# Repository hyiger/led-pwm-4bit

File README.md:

# led-pwm-4bit

A 40 × 30 mm two-layer board that dims a 24 V LED strip to one of 16 levels set by
four open-drain outputs of a Prusa GPIO Hackerboard. An ATtiny412 reads the 4-bit
word and drives a low-side N-MOSFET with 10-bit PWM at about 2.4 kHz.

KiCad 10 project. The design brief is [docs/spec.md](docs/spec.md) and the
reference netlist is [docs/netlist.txt](docs/netlist.txt).

## Status

| Step | State |
|---|---|
| Schematic | Done. ERC: 0 violations. `check_netlist.py`: matches `docs/netlist.txt` |
| Placement | Done. Schematic parity clean |
| Routing | In progress. DRC: 0 violations; 5 unrouted connections (three `HB_GND` links to F2, UPDI_BUS R11–D3, SEL3 C8–R10). GND pours stitched with 32 vias |
| Parts | Every line has a manufacturer part carried by Mouser; see [Parts](#parts) |
| Firmware | Not started (spec section 9) |

## Files

| Path | Contents |
|---|---|
| `led-pwm-4bit.kicad_pro` | Project: JLCPCB constraints, net classes (Default, Power) |
| `led-pwm-4bit.kicad_sch` | Schematic, one sheet, KiCad standard symbols only |
| `led-pwm-4bit.kicad_pcb` | Board |
| `led-pwm-4bit.kicad_dru` | Custom DRC rules (JLCPCB limits, 0.5 mm power tracks) |
| `check_netlist.py` | Compares the schematic netlist with `docs/netlist.txt` |
| `scripts/export-fab.sh` | Runs ERC, netlist check and DRC, then writes `fab/` |
| `fab/` | Schematic PDF, BOM, Mouser order CSV, position file, renders; Gerbers once DRC is clean |

## Parts

All parts are chosen from manufacturers Mouser stocks, and each was checked against
its manufacturer's datasheet for package, pinout and ratings. Capacitor values were
also checked against DC-bias data.
`fab/led-pwm-4bit-bom.csv` is the full BOM and `fab/led-pwm-4bit-mouser-order.csv`
is in Mouser's BOM-tool format (`BOARDS=n scripts/export-fab.sh` scales it). The
order rounds the resistors, capacitors and D3 up to at least 10 with spares, which
costs less than the exact count at Mouser's single-piece prices.

The Mouser part-number column is left empty on purpose. Mouser blocks automated
access, so no Mouser number could be read off its live listing, and a guessed
number can import cleanly and still be the wrong part. Mouser's BOM tool matches
each line on the manufacturer part number instead. Once a Mouser number is
confirmed, add a field named `Mouser` to that symbol and the export carries it.

| Ref | Part | Notes |
|---|---|---|
| U1 | Microchip MCP1792T-3302H/CB | 55 V input LDO, SOT-23A |
| U2 | Microchip ATTINY412-SSN | Tube; ATtiny212-SSN also fits |
| Q1 | ROHM RTR030N05HZGTL | 45 V, RDS(on) ≤ 95 mΩ at VGS 2.5 V. The 60 V IRLML0060 is not rated below 4.5 V gate drive |
| D1, D2 | Diodes Inc B160-13-F | 60 V 1 A Schottky, SMA |
| D3 | onsemi BAT54HT1G | SOD-323, pin 1 cathode (BAT54J is out of stock at Mouser) |
| F1 | Littelfuse 1812L050/60MR | 0.5 A hold, 60 V, Imax 10 A |
| F2 | Bel Fuse 0ZCG0010FF2C | 0.1 A hold, 60 V, Imax 100 A; Hackerboard/programmer ground return |
| C1 | Murata GRM188R61H225KE11D | 2.2 µF 50 V X5R 0603, about 0.4 µF at 24 V |
| C2, C9 | Murata GRM31CR71H475MA12L | 4.7 µF 50 V X7R 1206, about 2.7 µF each at 24 V |
| C3 | Samsung CL10A106MP8NQWC | 10 µF 10 V X5R 0603, about 5.9 µF at 3.3 V |
| C4 | KEMET C0603C104K5RACTU | 100 nF 50 V X7R |
| C5–C8 | KEMET C0603C103K5RACTU | 10 nF 50 V X7R |
| R1–R11 | YAGEO RC0603FR-07…L | 1 % 0603; R3–R10 are all 10 kΩ |
| J1, J2 | Phoenix Contact 1984617 | PT 1,5/2-3,5-H, the part the footprint is drawn for |
| J3 | Würth 61300511121 | 1×5 2.54 mm header |
| J4 | Würth 61300611121 | 1×6 2.54 mm header |

No 10 µF 50 V X7R in 1206 was in stock at Mouser. The Murata 4.7 µF X7R keeps more
capacitance at 24 V than any 10 µF 1206 part Mouser stocks.

## Routing notes

- The Power net class (`+24V_IN`, `VIN_F`, `+24V`, `LED_NEG`, `GND`) defaults to
  0.5 mm, and DRC rejects anything narrower. Signals default to 0.25 mm.
- Rule areas keep tracks off B.Cu under Q1 and U2, so the bottom pour stays whole
  there (spec section 8). Ground vias are still allowed.
- Return Q1's source (pin 2) straight to the GND pad of C2.
- The pours are stitched with 32 GND vias (0.6/0.3 mm, tented): one beside each
  GND pad, two between C9 and U1, plus a sparse 8 mm grid. The +24V and +3V3
  tracks split the top pour into regions joined only by thin necks, and the vias
  tie every region to the bottom pour. The vias stay clear of the routes still to
  be drawn and of the mounting-hole keepout, and no via drill lands on
  silkscreen. A few via rings reach under the edge of a part outline; they are
  tented, so this is cosmetic.
- C6 pad 2 had only one thermal spoke because SEL1 and SEL2 crowd it. It now has a
  0.5 mm GND track to a via at (125.75, 108.75).
- `HB_GND` joins J3 pin 1, J4 pins 1–2 and F2 pad 1. A 0.25 mm track is enough,
  and it survives the brief fault current before F2 trips. J3.1 to J4.1 runs easily
  on B.Cu. Keep it out of the GND pour: F2 is the only connection between the two
  grounds.
- `scripts/export-fab.sh` refills the pours before its DRC, without saving the board.

## Wiring and mounting

- Fuse the 24 V feed at the source: a 2–3 A fast fuse (rated ≥ 32 V DC) in the +
  lead at the PSU or tap point, or a separate 1–2 A supply. F1 is rated to interrupt
  only 10 A and does not protect the J1 cable.
- Run the supply's − wire straight to J1 pin 2. Don't share it with the Hackerboard
  cable's ground, so only signal current flows through the Hackerboard ground.
- Check the strip wiring for a short between + and − before the first power-up.
- Mount the board on standoffs with nylon screws, or keep metal hardware away from any
  grounded frame. The mounting holes have no copper around them.
- Avoid hot-plugging J1 at 28 V with long leads (see Open items).

## Connectors

| | Pin 1 | Pin 2 | Pin 3 | Pin 4 | Pin 5 | Pin 6 |
|---|---|---|---|---|---|---|
| J1 24 V in | +24 V | GND | | | | |
| J2 LED strip | Strip + | Strip − | | | | |
| J3 Hackerboard J6 pins 1–5 | GND (via F2) | out0 | out1 | out2 | out3 | |
| J4 FTDI adapter | GND (via F2) | CTS (GND via F2) | VCC (n.c.) | TXD | RXD / UPDI | DTR (n.c.) |

Hackerboard J6 is a 1×10 2.54 mm footprint, usually bare holes. Its pin 1 is the
square pad by the `GND` label at the `0` end. A straight 1×5 cable from J6 pins 1–5
to J3 matches pin for pin.

## Flashing

J4 takes any USB-serial adapter in the standard FTDI pin order with **3.3 V logic**
(FT232R, CP2102, or a CH340 that really runs at 3.3 V). The SerialUPDI network
(D3 and R11) is on the board, so the adapter needs no modification.

1. Power the board from 24 V. J4's VCC pin is not connected.
2. Plug the adapter in with its GND on J4 pin 1 (the `GND` end of the header).
3. Flash with avrdude 8.x:

   ```bash
   avrdude -c serialupdi -p t412 -P /dev/cu.usbserial-XXXX -U flash:w:firmware.hex:i
   ```

   or pymcuprog:

   ```bash
   pymcuprog write -t uart -u /dev/cu.usbserial-XXXX -d attiny412 -f firmware.hex --erase --verify
   ```

Keep the default 115200 baud at 3.3 V. In the Arduino IDE with megaTinyCore, pick
"SerialUPDI - SLOW: 57600 baud", a 10 MHz clock and BOD 2.6 V. Never change the
UPDI/reset pin fuse: recovery would then need a 12 V programmer.

A Microchip programmer (Atmel-ICE, MPLAB SNAP, PICkit) connects to J4 pin 5 (UPDI)
and pin 1 (GND), with its target-voltage sense lead on TP2 (+3V3) and the board
powered from 24 V. Leave "power target from tool" off.

## Using it from the printer

```gcode
M267 R3 B0    ; once: all expander pins are outputs (firmware default)
M267 R1 B15   ; level 15 (full on); B0 = off, B1..B14 in between
```

The level persists in the printer's EEPROM. While the printer boots, or when the
cable is unplugged, the inputs float high and the strip is off.

## Checks

```bash
python3 check_netlist.py
```

```bash
scripts/export-fab.sh
```

The script runs ERC (`--severity-all --exit-code-violations`), the netlist check and
DRC with `--schematic-parity` after refilling the pours. It writes Gerbers and
separate plated and non-plated drill files only when DRC reports no violations and
no unrouted connections.

## Changes from spec Rev 0.1

- Resistors and small capacitors are 0603. The 47 µF electrolytic is replaced by two
  4.7 µF 50 V X7R 1206 MLCCs (C2, C9), because no 50 V bulk part exists in 0603.
- J4 is a 6-pin FTDI-style header with a SerialUPDI network (D3, R11 470 Ω)
  instead of a bare 3-pin UPDI header.
- SEL pins are permuted for a crossing-free layout: SEL0 = PA2, SEL1 = PA1,
  SEL2 = PA7, SEL3 = PA6. Section 6 of the spec allows this.
- Q1 is a ROHM RTR030N05HZGTL (45 V) instead of the AO3422 (55 V), which Mouser
  does not carry.
- F2 puts the Hackerboard and programmer grounds (net `HB_GND`) behind a 0.1 A PPTC,
  and R7–R10 are 10 kΩ instead of 1 kΩ.
- Board constraints follow JLCPCB's 2-layer 1 oz capabilities. The design net
  classes keep the spec's 0.2 mm clearance and 0.25 / 0.5 mm tracks.

## Open items

- **Reverse polarity with a shared ground.** D1 protects only the board's own +24V
  rail. If the supply shares ground with the printer and the J1 wires are swapped,
  board GND rises to supply +. F2 then trips and stops the short through the
  Hackerboard ground, and the 10 kΩ R7–R10 keep the current into the input pins to
  about 2.4 mA each. Two exposures remain:
  - The pull-ups R3–R6 draw up to about 11 mA out of +3V3, pulling it about 0.6 V
    below GND. That is past the U1 and U2 supply-pin limits. A Schottky clamp from GND
    to +3V3 would fix it.
  - A programming adapter plugged in at the same time sees 41–57 mA through R11, which
    burns R11 (0.8–1.5 W) and stresses U2's UPDI pin and the adapter. Check J1
    polarity before plugging in an adapter.
  A reverse-polarity MOSFET in the J1 return would remove both by keeping board GND
  from rising at all.
- **Strip short.** F1 protects the wiring and D1, not Q1. A short across J2 while the
  strip is lit can destroy Q1 (3 A continuous, 12 A for 10 µs). A failed Q1 usually
  shorts and leaves the strip on. Replace Q1 after any strip short.
- **Hot-plug overshoot.** The all-ceramic 24 V input rings when J1 is hot-plugged, and
  D1 holds the peak on +24V. At 24 V with leads of 2 m or less the first peak is about
  30–36 V. At 28 V with heavy leads and F1 near its minimum resistance it can reach
  45–50 V, above Q1's 45 V and the capacitors' 50 V rating. A 47 µF 50 V electrolytic
  on +24V would damp it to under 30 V.
- Prusa lists the Core One INDX as *not compatible* with the GPIO Hackerboard, although
  firmware 6.9.1 and 6.10.1 still enable the M262–M268 commands on it.
- JLCPCB charges a small-board fee when a side is 30 mm or less. 40 × 31 mm avoids it.

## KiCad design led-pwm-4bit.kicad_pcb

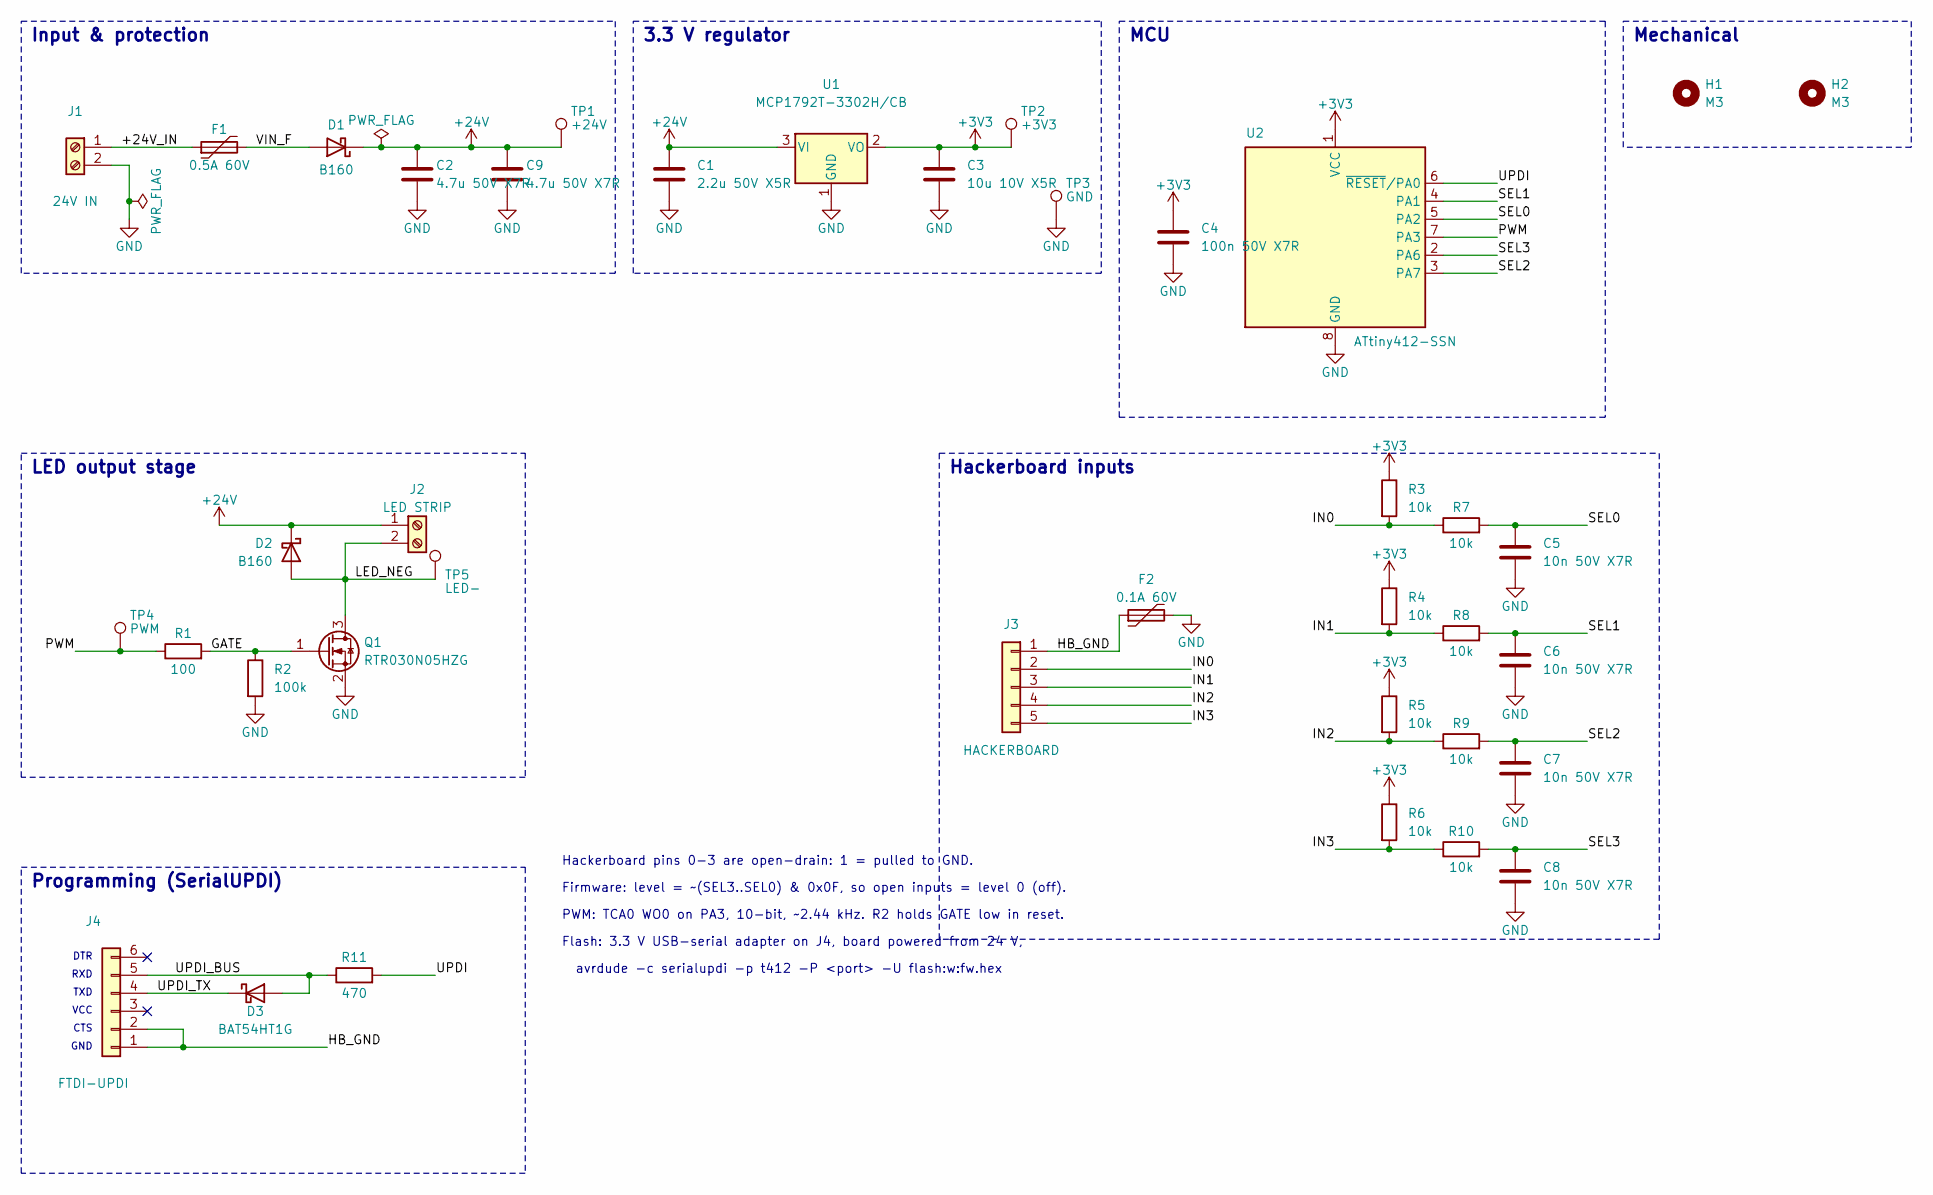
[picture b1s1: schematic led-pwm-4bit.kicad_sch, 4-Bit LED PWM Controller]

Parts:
C1: 2.2u 50V X5R; C_0603_1608Metric; MPN GRM188R61H225KE11D
C2, C9: 4.7u 50V X7R; C_1206_3216Metric; MPN GRM31CR71H475MA12L
C3: 10u 10V X5R; C_0603_1608Metric; MPN CL10A106MP8NQWC
C4: 100n 50V X7R; C_0603_1608Metric; MPN C0603C104K5RACTU
C5, C6, C7, C8: 10n 50V X7R; C_0603_1608Metric; MPN C0603C103K5RACTU
D1, D2: B160; D_SMA; MPN B160-13-F
D3: BAT54HT1G; D_SOD-323; MPN BAT54HT1G
F1: 0.5A 60V; Fuse_1812_4532Metric; MPN 1812L050/60MR
F2: 0.1A 60V; Fuse_1812_4532Metric; MPN 0ZCG0010FF2C
H1, H2: M3; MountingHole_3.2mm_M3
J1: 24V IN; TerminalBlock_Phoenix_PT-1,5-2-3.5-H_1x02_P3.50mm_Horizontal; MPN 1984617
J2: LED STRIP; TerminalBlock_Phoenix_PT-1,5-2-3.5-H_1x02_P3.50mm_Horizontal; MPN 1984617
J3: HACKERBOARD; PinHeader_1x05_P2.54mm_Vertical; MPN 61300511121
J4: FTDI-UPDI; PinHeader_1x06_P2.54mm_Vertical; MPN 61300611121
Q1: RTR030N05HZG; SOT-23; MPN RTR030N05HZGTL
R1: 100; R_0603_1608Metric; MPN RC0603FR-07100RL
R2: 100k; R_0603_1608Metric; MPN RC0603FR-07100KL
R3, R4, R5, R6, R7, R8, R9, R10: 10k; R_0603_1608Metric; MPN RC0603FR-0710KL
R11: 470; R_0603_1608Metric; MPN RC0603FR-07470RL
TP1: +24V; TestPoint_Pad_D1.0mm
TP2: +3V3; TestPoint_Pad_D1.0mm
TP3: GND; TestPoint_Pad_D1.0mm
TP4: PWM; TestPoint_Pad_D1.0mm
TP5: LED-; TestPoint_Pad_D1.0mm
U1: MCP1792T-3302H/CB; SOT-23; MPN MCP1792T-3302H/CB
U2: ATtiny412-SSN; SOIC-8_3.9x4.9mm_P1.27mm; MPN ATTINY412-SSN

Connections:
+3V3: C3.1, C4.1, R3.1, R4.1, R5.1, R6.1, TP2.1, U1.2 (VO), U2.1 (VCC)
+24V: C1.1, C2.1, C9.1, D1.1 (K), D2.1 (K), J2.1, TP1.1, U1.3 (VI)
/+24V_IN: F1.1, J1.1
/GATE: Q1.1 (G), R1.2, R2.1
/HB_GND: F2.1, J3.1, J4.1, J4.2
/IN0: J3.2, R3.2, R7.1
/IN1: J3.3, R4.2, R8.1
/IN2: J3.4, R5.2, R9.1
/IN3: J3.5, R6.2, R10.1
/LED_NEG: D2.2 (A), J2.2, Q1.3 (D), TP5.1
/PWM: R1.1, TP4.1, U2.7 (PA3)
/SEL0: C5.1, R7.2, U2.5 (PA2)
/SEL1: C6.1, R8.2, U2.4 (PA1)
/SEL2: C7.1, R9.2, U2.3 (PA7)
/SEL3: C8.1, R10.2, U2.2 (PA6)
/UPDI: R11.2, U2.6 (~RESET/PA0)
/UPDI_BUS: D3.2 (A), J4.5, R11.1
/UPDI_TX: D3.1 (K), J4.4
/VIN_F: D1.2 (A), F1.2
GND: C1.2, C2.2, C3.2, C4.2, C5.2, C6.2, C7.2, C8.2, C9.2, F2.2, J1.2, Q1.2 (S), R2.2, TP3.1, U1.1 (GND), U2.8 (GND)

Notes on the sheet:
MCU
TXD
Flash: 3.3 V USB-serial adapter on J4, board powered from 24 V,
Mechanical
Hackerboard pins 0-3 are open-drain: 1 = pulled to GND.
PWM: TCA0 WO0 on PA3, 10-bit, ~2.44 kHz. R2 holds GATE low in reset.
avrdude -c serialupdi -p t412 -P <port> -U flash:w:fw.hex
RXD
3.3 V regulator
Programming (SerialUPDI)
DTR
VCC
Input & protection
Firmware: level = ~(SEL3..SEL0) & 0x0F, so open inputs = level 0 (off).
CTS
GND
LED output stage
Hackerboard inputs

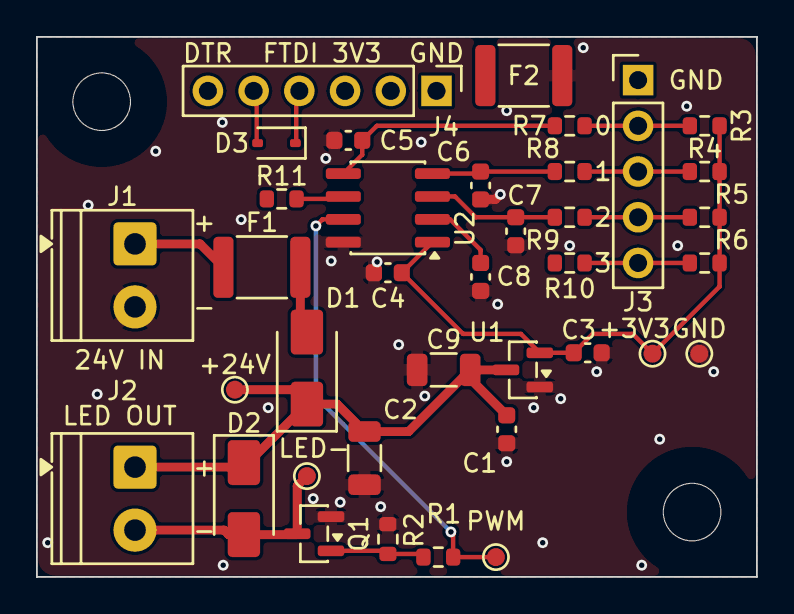
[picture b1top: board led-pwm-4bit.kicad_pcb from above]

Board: 2 copper layers, 40.0 x 30.0 mm, 39 parts (0 on the bottom side), 20 nets.

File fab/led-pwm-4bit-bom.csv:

"Reference","Value","Footprint","Manufacturer","MPN","Mouser","Qty"
"C1","2.2u 50V X5R","Capacitor_SMD:C_0603_1608Metric","Murata","GRM188R61H225KE11D","","1"
"C2,C9","4.7u 50V X7R","Capacitor_SMD:C_1206_3216Metric","Murata","GRM31CR71H475MA12L","","2"
"C3","10u 10V X5R","Capacitor_SMD:C_0603_1608Metric","Samsung","CL10A106MP8NQWC","","1"
"C4","100n 50V X7R","Capacitor_SMD:C_0603_1608Metric","KEMET","C0603C104K5RACTU","","1"
"C5-C8","10n 50V X7R","Capacitor_SMD:C_0603_1608Metric","KEMET","C0603C103K5RACTU","","4"
"D1,D2","B160","Diode_SMD:D_SMA","Diodes Inc","B160-13-F","","2"
"D3","BAT54HT1G","Diode_SMD:D_SOD-323","onsemi","BAT54HT1G","","1"
"F1","0.5A 60V","Fuse:Fuse_1812_4532Metric","Littelfuse","1812L050/60MR","","1"
"F2","0.1A 60V","Fuse:Fuse_1812_4532Metric","Bel Fuse","0ZCG0010FF2C","","1"
"J1","24V IN","TerminalBlock_Phoenix:TerminalBlock_Phoenix_PT-1,5-2-3.5-H_1x02_P3.50mm_Horizontal","Phoenix Contact","1984617","","1"
"J2","LED STRIP","TerminalBlock_Phoenix:TerminalBlock_Phoenix_PT-1,5-2-3.5-H_1x02_P3.50mm_Horizontal","Phoenix Contact","1984617","","1"
"J3","HACKERBOARD","Connector_PinHeader_2.54mm:PinHeader_1x05_P2.54mm_Vertical","Wurth Elektronik","61300511121","","1"
"J4","FTDI-UPDI","Connector_PinHeader_2.54mm:PinHeader_1x06_P2.54mm_Vertical","Wurth Elektronik","61300611121","","1"
"Q1","RTR030N05HZG","Package_TO_SOT_SMD:SOT-23","ROHM","RTR030N05HZGTL","","1"
"R1","100","Resistor_SMD:R_0603_1608Metric","YAGEO","RC0603FR-07100RL","","1"
"R2","100k","Resistor_SMD:R_0603_1608Metric","YAGEO","RC0603FR-07100KL","","1"
"R3-R10","10k","Resistor_SMD:R_0603_1608Metric","YAGEO","RC0603FR-0710KL","","8"
"R11","470","Resistor_SMD:R_0603_1608Metric","YAGEO","RC0603FR-07470RL","","1"
"U1","MCP1792T-3302H/CB","Package_TO_SOT_SMD:SOT-23","Microchip","MCP1792T-3302H/CB","","1"
"U2","ATtiny412-SSN","Package_SO:SOIC-8_3.9x4.9mm_P1.27mm","Microchip","ATTINY412-SSN","","1"
